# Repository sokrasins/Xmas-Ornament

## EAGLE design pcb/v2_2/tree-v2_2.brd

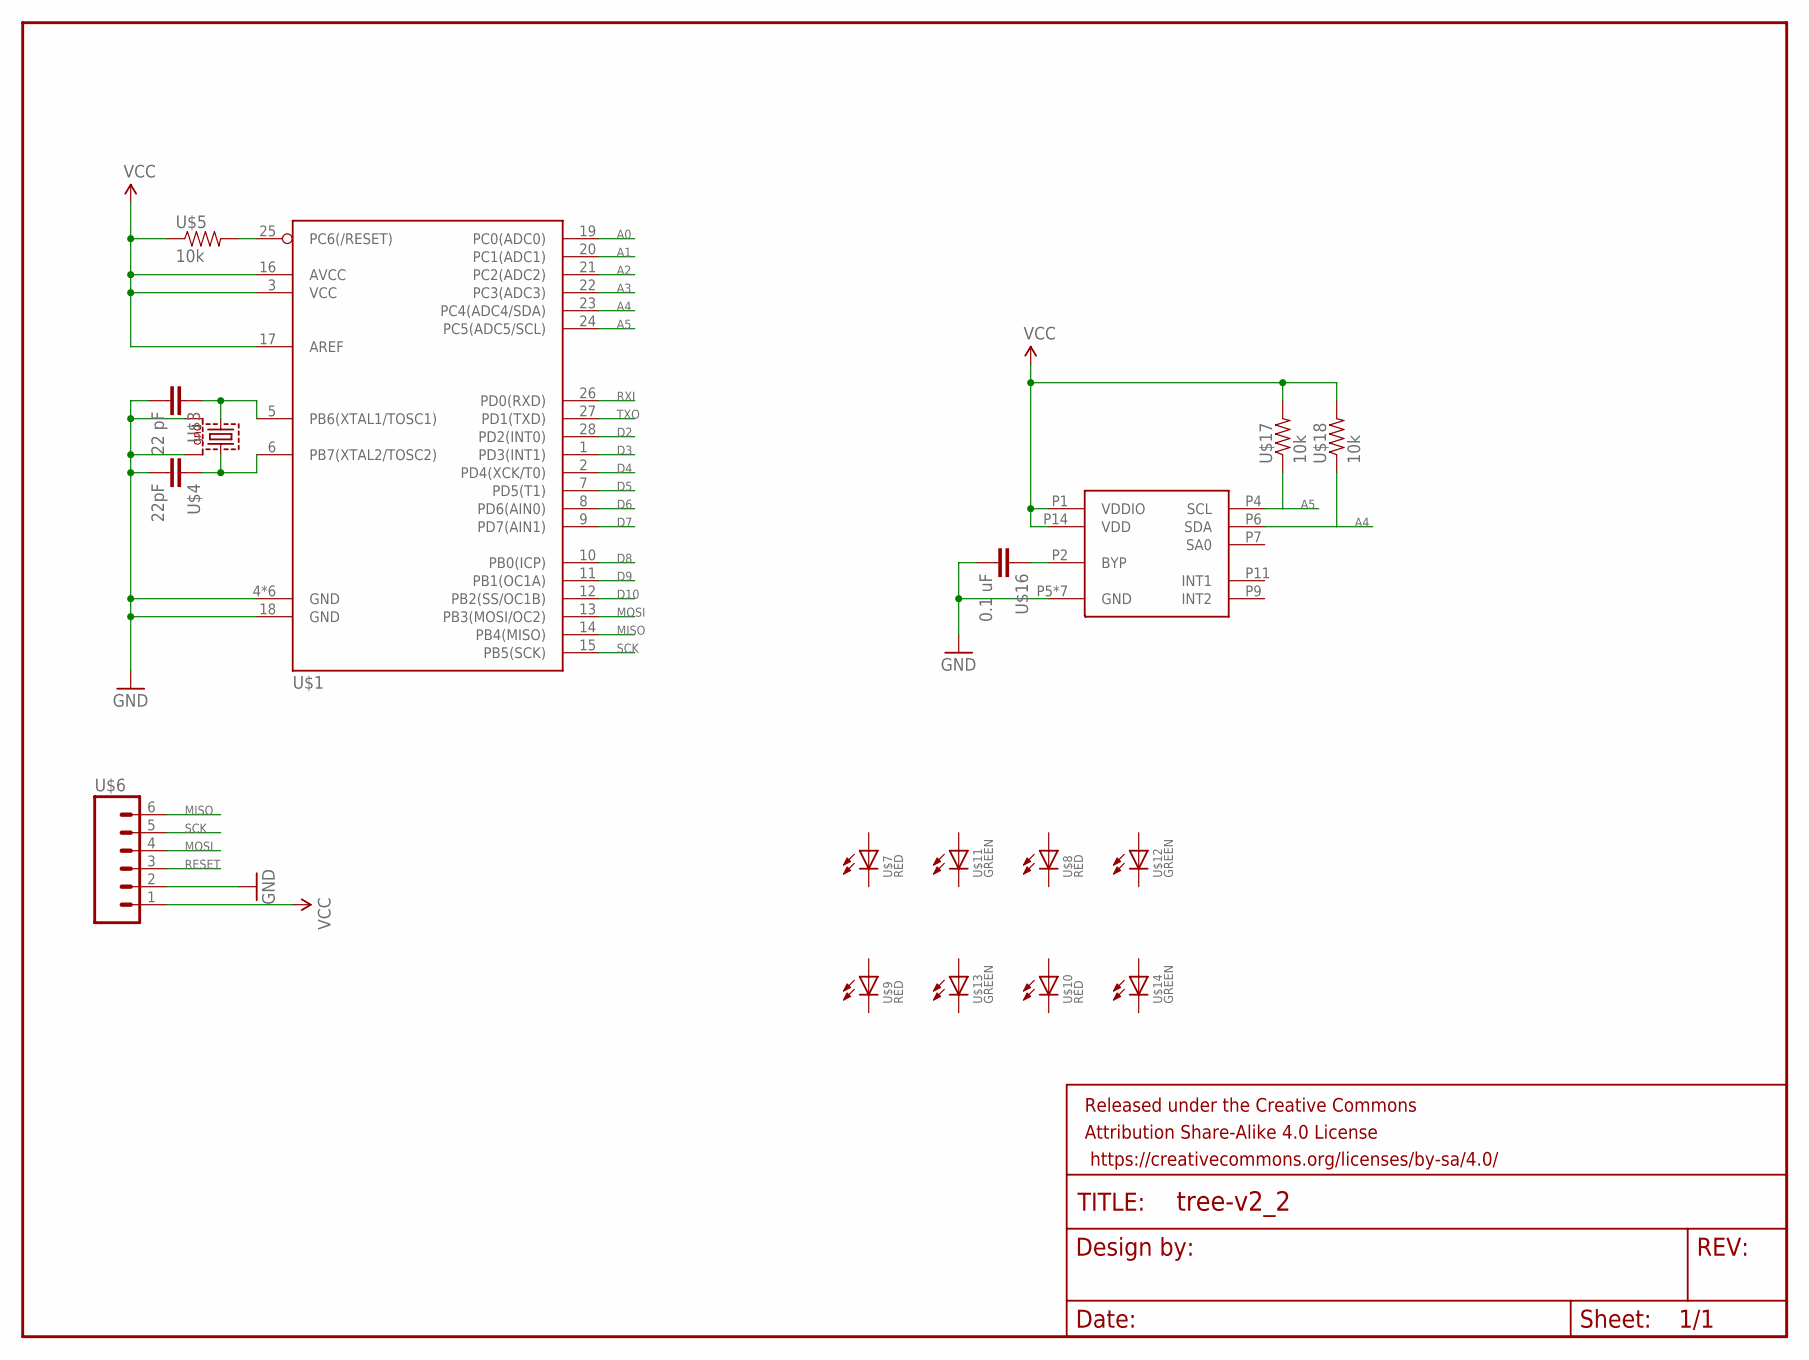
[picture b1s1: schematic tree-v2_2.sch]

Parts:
FRAME1: FRAME-LETTER; CREATIVE_COMMONS
U$1: ATMEGA168-28PINVFQFN-28; VQFN28
U$2: CRYSTAL-SMD-7B-SERIES-TXC; CRYSTAL-SMD-7B-SERIES-5X3.2MM
U$3: 22 pF; CAP-0603
U$4: 22pF; CAP-0603
U$5, U$17, U$18: 10k; RES-0603
U$6: HRD-60.1INCH_NO_SILKSCREEN; SIP6-SM-0.1IN-NOS.S.
U$7, U$8, U$9, U$10: RED; LED-1206
U$11, U$12, U$13, U$14: GREEN; LED-1206
U$15: MMA_8452; QFN-16-MMA
U$16: 0.1 uF; CAP-0603

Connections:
A0: U$1.19 (PC0(ADC0))
A1: U$1.20 (PC1(ADC1))
A2: U$1.21 (PC2(ADC2))
A3: U$1.22 (PC3(ADC3))
A4: U$1.23 (PC4(ADC4/SDA)), U$15.P6 (SDA), U$18.1
A5: U$1.24 (PC5(ADC5/SCL)), U$15.P4 (SCL), U$17.1
D2: U$1.28 (PD2(INT0))
D3: U$1.1 (PD3(INT1))
D4: U$1.2 (PD4(XCK/T0))
D5: U$1.7 (PD5(T1))
D6: U$1.8 (PD6(AIN0))
D7: U$1.9 (PD7(AIN1))
D8: U$1.10 (PB0(ICP))
D9: U$1.11 (PB1(OC1A))
D10: U$1.12 (PB2(SS/OC1B))
GND: U$1.4 (GND), U$1.18 (GND), U$1.TH (GND), U$1.TH@1 (GND), U$1.TH@2 (GND), U$1.TH@3 (GND), U$1.TH@4 (GND), U$2.P$2 (2), U$2.P$4 (4), U$3.2, U$4.2, U$6.2, U$15.P5 (GND), U$15.P8 (GND), U$15.P10 (GND), U$15.P12 (GND), U$15.P13 (GND), U$15.P15 (GND), U$15.P16 (GND), U$16.2
MISO: U$1.14 (PB4(MISO)), U$6.6
MOSI: U$1.13 (PB3(MOSI/OC2)), U$6.4
unnamed: U$1.5 (PB6(XTAL1/TOSC1)), U$2.P$1 (1), U$3.1
unnamed: U$1.6 (PB7(XTAL2/TOSC2)), U$2.P$3 (3), U$4.1
unnamed: U$15.P2 (BYP), U$16.1
RESET: U$1.25 (PC6(/RESET)), U$5.2, U$6.3
RXI: U$1.26 (PD0(RXD))
SCK: U$1.15 (PB5(SCK)), U$6.5
TXO: U$1.27 (PD1(TXD))
VCC: U$1.3 (VCC), U$1.16 (AVCC), U$1.17 (AREF), U$5.1, U$6.1, U$15.P1 (VDDIO), U$15.P14 (VDD), U$17.2, U$18.2

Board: 2 copper layers, 19 parts (0 on the bottom side), 11 nets, no tracks yet.

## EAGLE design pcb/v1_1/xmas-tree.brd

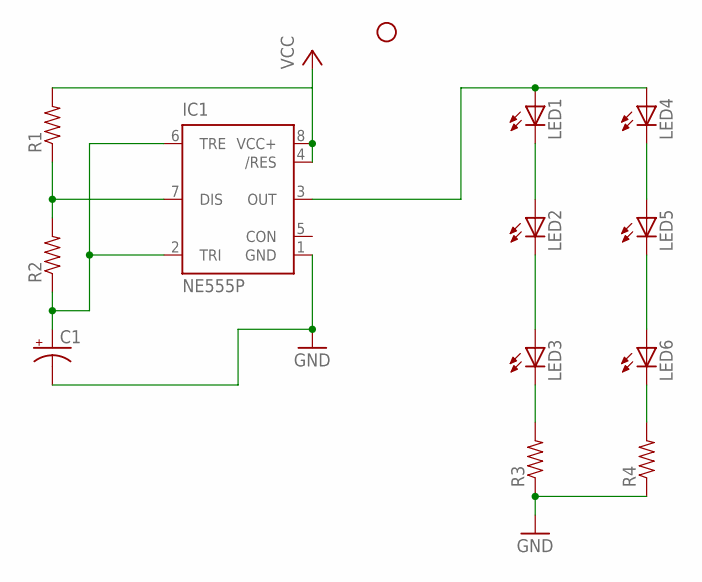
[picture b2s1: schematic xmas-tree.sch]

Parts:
C1: CAP_POLPTH2; CPOL-RADIAL-10UF-25V
IC1: NE555P; DIL-08
LED1, LED2, LED3, LED4, LED5, LED6: LED5MM
R1, R2, R3, R4: RESISTORAXIAL-0.3; AXIAL-0.3
STANDOFF1: STAND-OFF

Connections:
GND: C1.2 (-), IC1.1 (GND), R3.P$1 (1), R4.P$1 (1)
unnamed: C1.1 (+), IC1.2 (TRI), IC1.6 (TRE), R2.P$1 (1)
unnamed: IC1.3 (OUT), LED1.A, LED4.A
unnamed: LED1.K (C), LED2.A
unnamed: LED2.K (C), LED3.A
unnamed: LED3.K (C), R3.P$2 (2)
unnamed: LED4.K (C), LED5.A
unnamed: LED5.K (C), LED6.A
unnamed: LED6.K (C), R4.P$2 (2)
unnamed: IC1.7 (DIS), R1.P$1 (1), R2.P$2 (2)
VCC: IC1.4 (/RES), IC1.8 (VCC+), R1.P$2 (2)

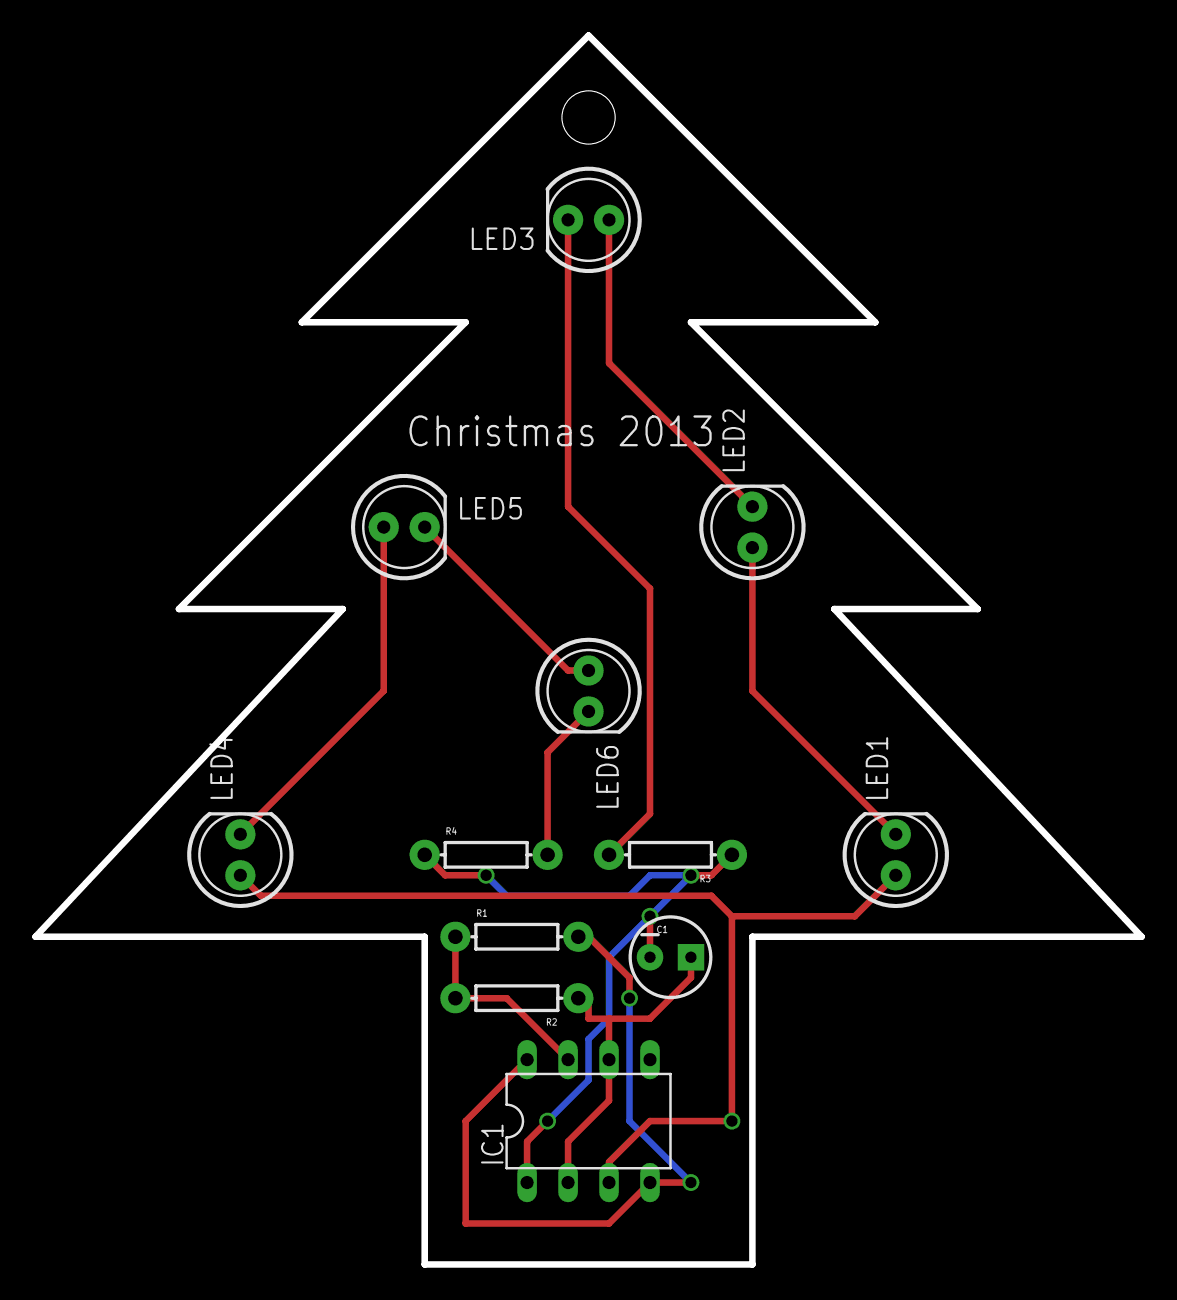
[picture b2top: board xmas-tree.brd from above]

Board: 4 copper layers, 68.6 x 76.2 mm, 13 parts (0 on the bottom side), 11 nets.

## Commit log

2014-09-28 Added docs, ver 1 brd, renamed repo
2014-09-29 Added datasheets, started schem

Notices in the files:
parts and their libraries:
SparkFun-Passives: Licensing: CC v3.0 Share-Alike You are welcome to use this library for commercial purposes.
SparkFun-Aesthetics: Licensing: Creative Commons ShareAlike 4.0 International - https://creativecommons.org/licenses/by-sa/4.0
SparkFun-Aesthetics: Released under the Creative Commons
